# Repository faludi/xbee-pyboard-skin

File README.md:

# xbee-pyboard-skin
XBee MicroPython Skin for pyboard

<h4>Background</h4>
The <a href="http://micropython.org">MicroPython project</a> created a reference design called the "<a href="http://docs.micropython.org/en/latest/pyboard/pyboard/quickref.html">pyboard</a>" that includes an ARM processor with USB connectivity, button and switch I/O, access to all pinouts and SD card storage. The pyboard layout accepts daughterboards, called "skins" including a couple official ones that support <a href="https://micropython.org/store/#/products/LCD32MKv1_0">LCD screens</a> and <a href="https://micropython.org/store/#/products/AMPv1_0">Audio</a>.

<h4>XBee Skin</h4>
The XBee Skin for MicroPython connects any through-hole XBee module directly to the reference pyboard. It supports the XBee's association indicator and RSSI signal strength output lights, and features a more conveniently positioned reset button for the pyboard itself.

<h4>Pinouts</h4>

The skin can be mounted in two different orientations, covering either the pyboard's "Y" or "X" set of pins. If you choose the "Y" pins it uses UART 6 and it you choose the "X" pins it uses UART 4.

<table>
  <tr>
    <th>Pin</th>
    <th>function</th>
    <th>pyboard</th>
    <th></th>
    <th>Pin</th>
    <th>function</th>
    <th>pyboard</th>
  </tr>
  <tr>
    <td>1</td>
    <td>RX</td>
    <td>Y1 or X1 (UART 6 or 4)</td>
    <td></td>
    <td>16</td>
    <td>n/c</td>
    <td></td>
  </tr>
  <tr>
    <td>2</td>
    <td>TX</td>
    <td>Y2 or X2 (UART 6 or 4)</td>
    <td></td>
    <td>15</td>
    <td>3.3V</td>
    <td>3.3V</td>
  </tr>
    <tr>
    <td>3</td>
    <td>RTS (optional)</td>
    <td>Y3 or X3</td>
    <td></td>
    <td>14</td>
    <td>GND</td>
    <td>GND</td>
  </tr>
    <tr>
    <td>4</td>
    <td>CTS (optional)</td>
    <td>Y4 or X4</td>
    <td></td>
    <td>13</td>
    <td>RESET (pyboard)</td>
    <td>RESET</td>
  </tr>
    <tr>
    <td>5</td>
    <td>n/c</td>
    <td></td>
    <td></td>
    <td>12</td>
    <td>SLEEP RQ</td>
    <td>Y12 or X12</td>
  </tr>
    <tr>
    <td>6</td>
    <td>n/c</td>
    <td></td>
    <td></td>
    <td>11</td>
    <td>STATUS (on/slp)</td>
    <td>Y11 or X11</td>
  </tr>
    <tr>
    <td>7</td>
    <td>n/c</td>
    <td></td>
    <td></td>
    <td>10</td>
    <td>n/c</td>
    <td></td>
  </tr>
    <tr>
    <td>8</td>
    <td>n/c</td>
    <td></td>
    <td></td>
    <td>9</td>
    <td>n/c</td>
    <td></td>
  </tr>
</table>

Building the board requires two off-the-shelf components:
<ul>
<li>2 - 10 pin <a href="https://www.sparkfun.com/products/116">0.1" male breakaway headers</a></li>
<li>2 - <a href="https://www.sparkfun.com/products/8272">2mm 10-pin female headers</a> used as the XBee socket</li>
</ul>

Optional components are:
<ul>
<li>2 - <a href="http://www.digikey.com/product-search/en?keywords=541-220GCT-ND">SMT 220 ohm resistors in 0603 package size</a></li>
<li>2 - <a href="https://www.digikey.com/product-search/en?keywords=511-1585-1-ND">SMT LEDs in 0603 package size</a></li>
<li>1 - <a href="https://www.sparkfun.com/products/8720">SMT tactile switch</a></li>
</ul>

Printed circuit boards can be ordered from <a href="https://oshpark.com/shared_projects/VDeE8qlG">OSH Park</a>.

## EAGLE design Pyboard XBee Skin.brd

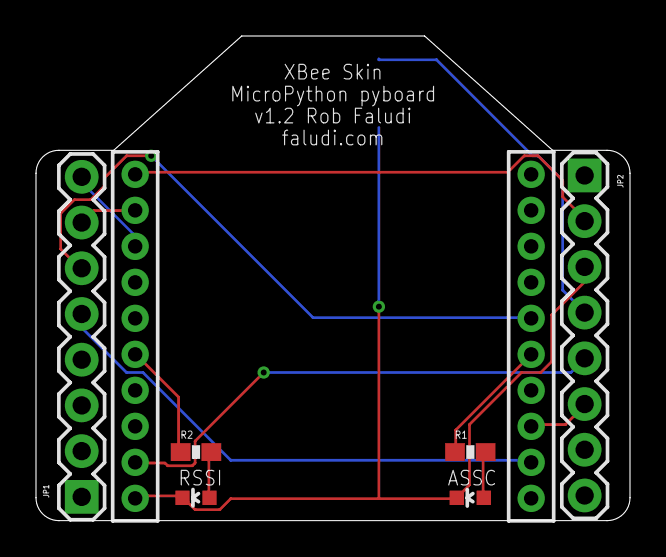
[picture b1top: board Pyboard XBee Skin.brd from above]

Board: 2 copper layers, 33.0 x 26.9 mm, 8 parts (1 on the bottom side), 13 nets.

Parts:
ASSC: LED-0603
JP1, JP2: 1X08
PYBOARD_RESET: TS-1188E; TACTILE_SWITCH_SMD
R1, R2: 0603-RES
RSSI: LED-0603
U$1: XBEE-1B1; XBEE-1

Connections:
3.3V: JP2.2, U$1.1
ASSC: R1.1, U$1.15
CTS: JP1.5, U$1.12
GND: ASSC.C, JP2.3, PYBOARD_RESET.3, RSSI.C, U$1.10
unnamed: R2.2, RSSI.A
unnamed: ASSC.A, R1.2
RESET: JP2.4, PYBOARD_RESET.1
RSSI: R2.1, U$1.6
RTS: JP1.6, U$1.16
SLP_CTRL: JP2.5, U$1.9
SLP_STATUS: JP2.6, U$1.13
XBEE_RX: JP1.8, U$1.3
XBEE_TX: JP1.7, U$1.2

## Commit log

2016-04-08 Board layout in PDF format
2016-04-08 Schematic in PDF format
2016-04-08 Eagle CAD board design file
2016-04-08 Eagle CAD schematic file
2016-04-08 project description and parts
2016-04-08 project description, parts and pinout
2016-04-17 project description, parts and pinout
    updated pinouts
2016-04-28 Board layout in PDF format
    updates to silkscreen and reposition reset button
2016-04-28 Schematic in PDF format
    new reset button
2016-04-28 Eagle CAD board design file v1.2
    updates to silkscreen and reposition reset button
2016-04-28 Eagle CAD schematic file v1.2
    new reset button
2016-04-28 version 1.2 updates

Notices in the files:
parts and their libraries:
SparkFun-Connectors: Licensing: CC v3.0 Share-Alike You are welcome to use this library for commercial purposes.
